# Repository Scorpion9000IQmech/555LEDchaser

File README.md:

# 555LEDchaser

I MADE A LED BLINKY BOARD FOR STASIS USING KICAD, IN THE SHAPE OF AN ANATOMICAL HEART WITH SIGNAGE WITH SENTIMENT TO ME!!!!

## PCB VIEW
---

## Schematic view
---

the heart is designed in a manner that the lights light up in the flow of blood, going from the right upper, right lower, left lower and finally left upper chamber of the heart
I made the project this way simply because I liked the idea of the heart; my passion for learning about health and by extension anatomy; I also liked how it served as a tribute to my friend, an expression through design of the project and the words written on it

this is my BOM, though I plan on just ordering it myself, and printing my case myself since I have a personal 3d printer
And here is the full assembly with my open top case and the PCB in the shape of an anatomical heart that lights up in the flow of blood.

\

## important tips
---
1. it is shown in the schematic, but the bottom pin in the two header pins connected to the board is the GND, and the upper is the +5V
2. The potentiometer can be replaced for three pinheaders and the potentiometer connected by a wire, depending on the potentiometer
3. the CD4017 is SMD, quite annoying to solder."
4. also shown in schematic but the anode of the led goes in the circle pad, and the GND in the square pad
5. the capacitors can be switched if they have the same values requires, but be wary of which hole the anode/cathode is being put in with cylindrical capacitors

## Physical example:
---

# BOM
| Item | price | source |
|---|---|---|
| Case | 8 USD | Local 3d printing buisness |
| PCB | 2 USD plus shipping | JLPCB |
| Componets | (meant to be no cost) | by hackclub(Mine never came, I sourced them locally) |

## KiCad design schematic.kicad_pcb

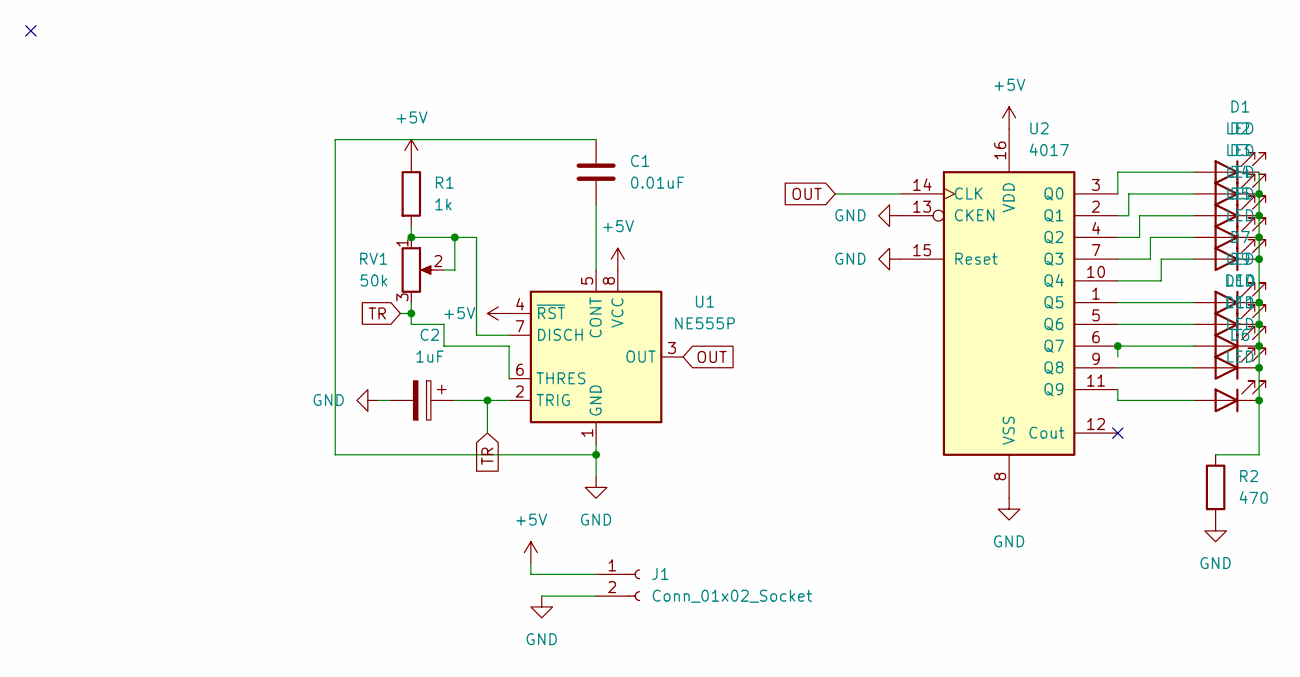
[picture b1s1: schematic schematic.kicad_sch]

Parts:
C1: 0.01uF; CP_Radial_D5.0mm_P2.00mm
C2: 1uF; C_Disc_D7.5mm_W2.5mm_P5.00mm
D1, D2, D3, D4, D5, D6, D7, D9, D10, D11: LED; LED_D3.0mm
J1: Conn_01x02_Socket; PinHeader_1x02_P2.54mm_Vertical
R1: 1k; R_Axial_DIN0207_L6.3mm_D2.5mm_P7.62mm_Horizontal
R2: 470; R_Axial_DIN0207_L6.3mm_D2.5mm_P7.62mm_Horizontal
RV1: 50k; Potentiometer_Vishay_T93YA_Vertical
U1: NE555P; DIP-8_W7.62mm
U2: 4017; NS16

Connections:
+5V: J1.1, R1.1, U1.4 (~RST), U1.8 (VCC), U2.16 (VDD)
GND: C1.2, C2.2, J1.2, R2.2, U1.1 (GND), U2.8 (VSS), U2.13 (CKEN), U2.15 (Reset)
unnamed: D1.2 (A), U2.3 (Q0)
unnamed: D1.1 (K), D2.1 (K), D3.1 (K), D4.1 (K), D5.1 (K), D6.1 (K), D7.1 (K), D9.1 (K), D10.1 (K), D11.1 (K), R2.1
unnamed: D2.2 (A), U2.2 (Q1)
unnamed: D3.2 (A), U2.4 (Q2)
unnamed: D4.2 (A), U2.7 (Q3)
unnamed: D5.2 (A), U2.10 (Q4)
unnamed: D6.2 (A), U2.11 (Q9)
unnamed: D7.2 (A), U2.1 (Q5)
unnamed: D9.2 (A), U2.5 (Q6)
unnamed: D10.2 (A), U2.6 (Q7)
unnamed: D11.2 (A), U2.9 (Q8)
unnamed: C1.1, U1.5 (CONT)
unnamed: R1.2, RV1.1, RV1.2, U1.7 (DISCH)
OUT: U1.3 (OUT), U2.14 (CLK)
TR: C2.1, RV1.3, U1.2 (TRIG), U1.6 (THRES)

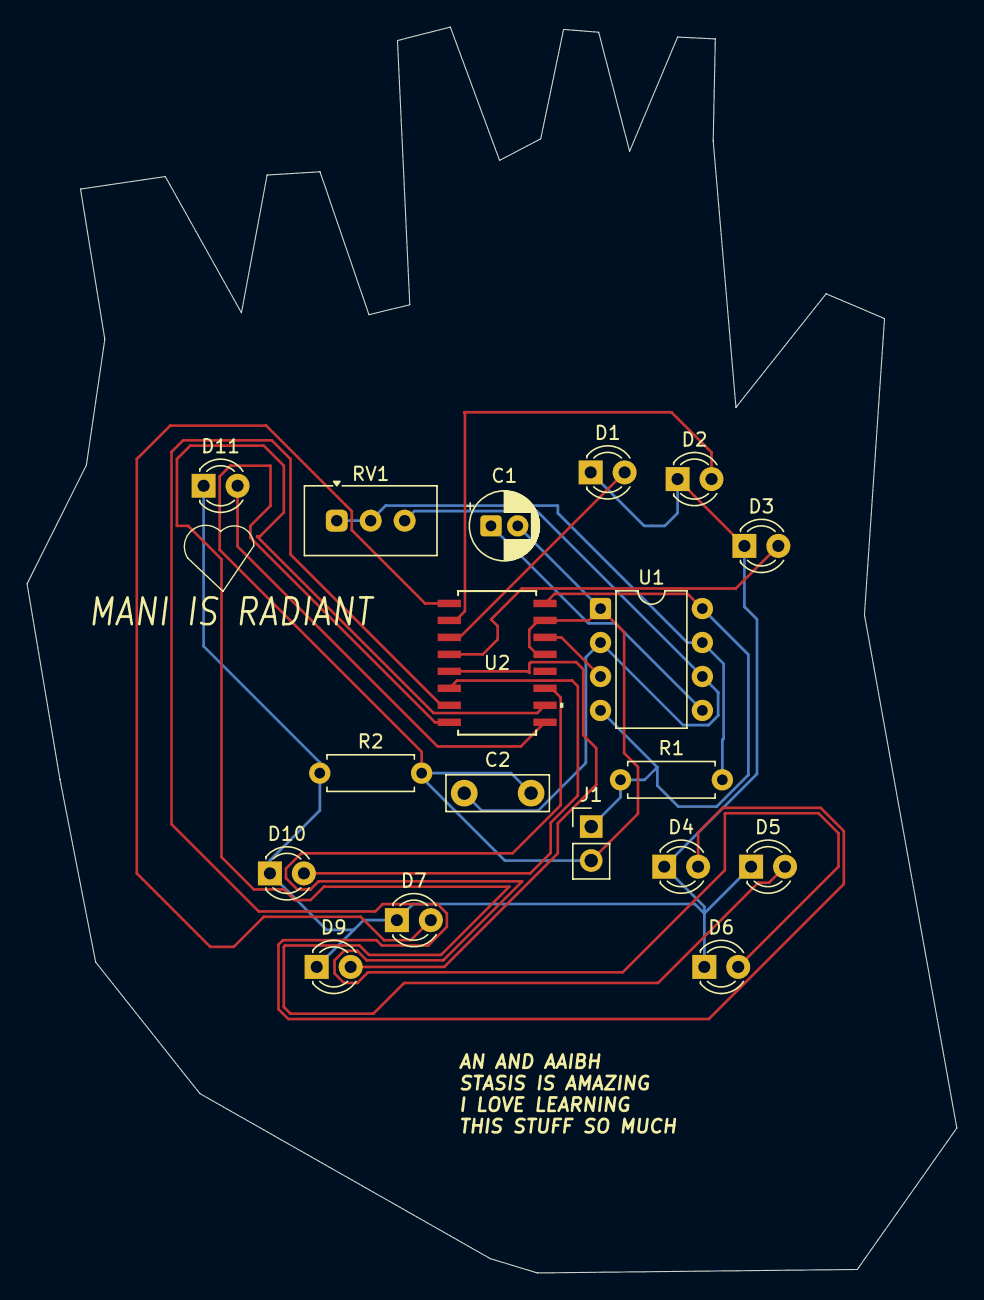
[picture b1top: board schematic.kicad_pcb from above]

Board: 2 copper layers, 69.6 x 93.2 mm, 18 parts (0 on the bottom side), 17 nets.

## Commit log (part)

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2026-04-09 Create bom
2026-04-09 Rename image_2026-03-17_175917722.png to images/image_2026-03-17_175917722.png
2026-04-09 Rename image_2026-03-18_231937216.png to images/image_2026-03-18_231937216.png
